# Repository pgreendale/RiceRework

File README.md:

# RiceR - A rework of the Rice contact mic preamp 

This project is based on the initial work of Alexander Rice and its successors especially the design from [Zach Poff](https://www.zachpoff.com/resources/alex-rice-piezo-preamplifier/), which caught my interest as a PCB layout was provided. He also mentions Charles Staffeld from [Sagittronics](https://sagittronics.wordpress.com/2019/07/04/simple-phantom-power-preamp-alex-rice-piezo-amplifier/), who has done extensive simulation of the original circuit. This is of significant importance looking into the input impedances of your mixing or recording device (whatever your phantom source is) putting load on the AC (signal-) path. 
That explained a lot to me when I was exploring reasons for the low gain performance of my built copies of the Rice preamp (around 9dB was the most common case). 

The design itself is [KISS](https://en.wikipedia.org/wiki/KISS_principle), it is understood and the mentioned sources provie good desings, so why these effords? 

Because we <b>can</b> (make it always better).

## Thoughts 
The <b>J201</b>-based design is biased around <i>0.5mA</i> current, [Sagittronics](https://sagittronics.wordpress.com/2019/07/04/simple-phantom-power-preamp-alex-rice-piezo-amplifier/) uses <b>2N3819</b>s with <i>1mA</i> current source. Double current means 4 times  signal power with $`P=I^2*R`$. Can we do more?

### Input impedance and source current
We want 1.228$`V_{eff}`$ (+ 4dBu) at our recorder inputs for a starting point. The design overall is a symmetrical differential amplifier, so we split our amplitude to 1/2 excursion from 0 to the <i>+</i> and <i>-</i> signal input. We assume 2 times 3.6k AC load in parallel (e.G. for Zoom recorders, Sagittronics mentioned) and get roughly

$`I = 2 \cdot I_{signal} = 2 \cdot \frac{\frac{1.228 V }{2}}{3.6kOhm}`$. 

This calculates to 0.171mA per line and sums up to <b>0.341mA</b>. In case of having less than .5mA available, we can experience gain degradation due to current-limiting at the source. This is why the 2N3819 variant does <b>14dB</b> Voltage gain at low input impedances, compared to my <i>measured 9dB</i> for the J201 configuration, around 6dB more amplitude. 

You can choose recorders with High-Z at their inputs to compensate for that, but if you're in the fields for recording, you may find restrictions at having only your already chosen and beloved recording device. Mixers like Mackie's [VLZ04](https://mackie.com/img/file_resources/1604VLZ4_OM.pdf) has 2.5k at its microphone inputs, thus fulfilling input impedance with 10 times the 220Ohm Microphone impedance, but also a non High-Z load in the AC path. 

### Maximum Voltage excursion
If we have an recorder with High-Z input, we can calculate the maximum voltage change at the 6.8k resistors from inside your recording devices phantom power circuit. They are used as drain resistors here, so current change means changing voltage drop at the resistors, the AC part (our signal) is decoupled internally with capacitors. At 0.5mA, there are +/- 0.25mA per (differential) signal input, if we change input so that one line goes towards up until Phantom power (zero current over the injection resistor), the other one is pulled down towards ground, we got $`V_{eff}=3.4 V`$ (from 0.5mA * 6.8k) difference at maximum (we avoid thinking about clipping, and the JFETs nonlinear behavior at this operating point). The biasing network around the gates keeps the gate at half of the voltage drop over the current source and the amplifying JFET. Both gates are <i>floating</i> somewhere near the phantom voltage potential. 

Piezo discs as contact mics have pretty high output voltages, so we dont need as much as voltage amplification as possible, but a fair amount of output voltage swing is nice to have,(Zoom doesnt specify maximum input voltages for their [Handy Recorder](https://www.zoom-europe.com/de/handy-recorder) products , Mackie says +22dBu maximum at mic inputs for the VLZ04). We need a stronger current source to go beyond +0dB at the output. 

### JFET Types
I like the J201, but it has poor performance. Note that more recently produced J201s have less maximum saturation current in general. I tried to find some employable alternatives. 

Since JFETs have their gate implemented as reverse biased diode, the Gate of the used N-Channel J201 etc. is biased negatively as seen from source. in the worst case, the gate is tied to ground and the source just hanging at full phantom voltage. So we need to widthstand breakdown voltages $`V_{GSS}`$ as great as -48V negative voltages. This limits the set of useable JFET types somewhat, but we can minimize that a by subtracting the current source drop. 

<b>Transconductance:</b>
Small voltage changes will cause greater current changes at higher $`g_m=\frac{\Delta i_{out}}{\Delta u_{in}}`$. This results in higher voltage drop changes at the phantom power resistors. Higher $`g_m`$, more gain. 

<b>Saturation Current:</b> 
The saturation current $`I_{DS}`$ is important for the current source. You'll tie the gate to ground and put a source resistor into the current path. The JFET will limit the current if the drop voltage of the resistor exceeds the JFETs cutoff voltage.  Some J201s have so low saturation currents that even the source resistor can be dropped, so that gate and source are tied directly to ground and the JFET is running in $`I_{DSS}`$ mode at zero gate voltage. 

Saving a resistor is not our goal. External noise on both amplifier inputs is causing the current source to change its bias voltage to stabilize the current. If it is not able to do that, the amplified noise is not symmetric on both signal lines (one side may experience earlier amplitude clipping due to unsymmetric current delivery) and can't be cancelled out by the differential recorder input stage. Having a greater range of voltage swing at the current source will allow more common mode range. Higher voltage drop at the current source allows amplifier JFETs with less gate to source voltage specs.  

<b>Fun</b>
InterFet has a really interesting outline of their JFETs on their [website](https://www.interfet.com/jfet-master-table/), based on the geometry. 

| JFET Type    | $`V_{GSS}`$ min | $`I_{DSS}`$ (min)| $`g_m`$ Transconductance (min)|Noise|
|-----|-----|-----|-----|-----|
|[J201](https://www.mouser.de/datasheet/2/676/jfet_j201_j202_interfet-2887411.pdf)|-40V| 0.2mA|500µS|5nV / Hz |
|[J202](https://www.mouser.de/datasheet/2/676/jfet_j201_j202_interfet-2887411.pdf)|-40V| 0.9mA|1000µS|5nV / Hz |
|[J113](https://www.mouser.de/datasheet/2/676/jfet_j111_j112_j113a_interfet-2887724.pdf)|-40V|2mA|15000µS|1.2nV / Hz|
|[J301](https://www.mouser.de/datasheet/2/676/jfet_j308_j309_j310_interfet-2887299.pdf)|-25V|24mA|8000 µS|2nV / Hz| 
|[BF245C](https://www.nxp.com/docs/en/data-sheet/BF245A-B-C.pdf)|-30V|12mA|14000µS||
|[2N3819](https://www.interfet.com/jfet-datasheets/jfet-2n3819-interfet.pdf)|-25V|2.0mA|2000µS|7nV / Hz|

Four things can be optimized: 

- More gain from transconductance
- Higher amplitude at phantom resistors from higher current variation
- Higher common mode noise suppression by allowing the currrent source to vary more  
- Less noise  

### Phantom Power
[DIN EN 61938](https://schoeps.de/fileadmin/user_upload/user_upload/Downloads/Vortraege_Aufsaetze/Mikrofonaufsaetze/Mikrofonbuch_Kap13.pdf) defines a current of 10mA at 48V phantom voltage (phantom current at + and - signal path together).

This <b>doesn't</b> mean that <i>every</i> recording device has the capability of driving full 10mA but lets assume we have half of that available with semiprofessional equipment. 5mA current sourcing gives 2.5mA per branch in the amplifier, giving room for gain and output improvements.

## Circuit	
Please look after [Simulation](/2-Simulation/Simulation.md) detailed circuits, simulations and results of the following approaches.  

### Approach 1: Current Source with more voltage excursion 
The J201 has a low cutoff voltage, so the voltage drop over the source resistor has is small (-0.3V min according to InterFET), asking for small resistor values to archieve this at operating point. Calculation gives 600Ohm, but in real life, I used smaller values around 100-150 Ohm to set the current output higher. This hinders the current source to lower output voltage if high common mode input puts both amplifying JFETs into conduction. 

Changing the current source J3 to a J202 JFET archives this, because it needs greater source resistor values to archieve the same current limit and allows for greater common mode input without clipping to ground.  

### Approach 2: J113 and J310 JFETs in Action
J113 and J310 have higher current specs. Especially the J310 in its function as current source is run far away from pinchoff Vg with higher source resistors. This enables the current source to float more up and down and allows more CMRR suppression down to -76dB while the amp itself provides <b>15dB</b> gain with <i>loaded</i> outputs. Plus less noise coming from the JFETS. 

### Approach 3: double current source 
A last experiment to get even more CMRR suppression requires more headroom at the current source. This is archieved to two current sources in serial configuration. Simulations show up additional -4dB CMRR, so its -80dB. Interestingly, the gain <i>rises</i> another 3.5dB too. Can't explain that at the moment. 

## PCB 
### THT vs. SMD

JFETs are still in use, but THT devices (with legs to be mounted through holes in your PCB) are kind of old-fashioned. Manufacturers know that and due to more smd-oriented PCB-Design nowadays, such components become more and more rare, thus difficult to get or <i>unreasonably</i> expensive. I didnt want to buy overpriced J201's from shady e**y stores or hipster-wallet oriented offers, and so I went on with the [SMD MMBFJ201](https://www.reichelt.de/n-kanal-jfet-40v-0-2-1ma-0-35w-sot-23-mmbfj201-p360202.html?&trstct=pos_0&nbc=1) of the J201, which costs less (0.30€)  of what a is asked for [THT J201](https://www.mouser.de/ProductDetail/InterFET/J201?qs=OxRSArmBDfyvD8SbvWteMw%3D%3D).

### Making Things smaller
My goal was to fit the whole preamp into an XLR plug. The metal housing is well grounded by the recorder and acts as shield for the amplifier. 

There are two <b>caveats</b>: capacitance/charge changes in the cable between preamp and piezo and also microphonic events like tapping the connectors housing can be heard. First is caused by the cable itself acting as a microphonic capacitor between ground and signal lines and second effect comes from the piezoelectricity of the ceramic SMD capacitors. SMD PP or PE caps in 0402 size were not available (if any ever?) so thats a tradeoff.

## Mass FET Matching
The amp is a differential (thus symmetric) design. To get good performance, matched components are needed, especially the JFETs whose can deviate from the specified mean value, even if they came from the same production run. Resistors and capacitors are easier to match, you can just buy them with good specs (1% SMD resistors are not as expensive as similiar THT maybe 20 years ago)

Not perfect, but good enough: 

 * Buy some run-of-the mill china copy of a [component tester](https://www.ebay.de/itm/265065551933?hash=item3db723583d:g:t-kAAOSwvWNgNhKa&amdata=enc%3AAQAIAAAA4MVZA11pXEi%2BY8FpUKZ%2Ba6fGrj%2Bg92W5g%2BvEFuaV7X8trvuxUWNuu%2BiUo3P4QnSn8eicAGEaVRB%2BaX3sno8Zs7n9p32MTcgCp%2FKcCjfit%2Bm41IrsrzKEI65ftT0AGj6qV5wsm%2BSe9ota6LyMAYbrZ3AixUm3jQbcnIuPTjFkVYe%2Big%2BgnT9Nog9wD%2F92axCRTxBFWWMISdoD28%2FKe9K8RMAzgf7rEN7JKfyHri0wTwoJ5zPvL857RYVo45sQIgmp1lrfoy2E4d%2F9Fjsllpe8T1pWKjBM68IU9CnFLe9h732N%7Ctkp%3ABk9SR4qI0vqmYw) based on the work of [Markus Frejek and Karl-Heinz Kübbeler](https://www.mikrocontroller.net/articles/AVR_Transistortester#Hint_to_Cloners_and_Sellers_中文). The versions with the 3 SMD pads next to the test socket are good for putting JFETS with SOT-3 housing on.
 * Get [firmware souce](https://github.com/Mikrocontroller-net/transistortester/tree/master) and compile it with UART support. (I had to replace my SPI display with an I2C oled one to free pins for UART, you can also remove the display)
 * Test components: put some on, press the button verify the measurement is done 
 * Label the components! My favorite is a [glued sheet](0-Documentation/JFET_Matching.jpeg) with a table with numbers, where I put freshly tested components on. 
 * Record the UART output into a file e.g. with [putty](https://putty.org) 
 * CSV import: Use MS Excel or Libreoffice Calc to get the test parameters from the uart record text file into a spreadsheet, convert it into a table that parameters from the same component stick together
 * sort for <b>IDss</b>, <b>ID0</b> and <b>V_g at pinchoff</b> and use the most similiar parts together (same readings)

|Transistor tester lunchbox|JFETs on labeled glue sheet|
|---|---|
|||

## Finished Preamp
### Building kit 
Finished preamp housed in XLR plug, above is a prepared building kit, including matched parts and PCB. 

### Measurements with real built High-Gain preamp
These measurements were done at 
 * 48V phantom power, 6.76k resistors 
 * -11.77 dbU (200mV to 0.775V)  amplitude of the input sine  
 * 10k load resistance, roughly 5 times greater than in simulations not good in terms of comparability

|Freq.| 35Hz| 1kHz |5KhZ | 28KHz |
|---|---|---|---|---|
||  | |||
|abs. Output|  9.68dBU, HP rolloff  | 15.72dBU  | 15.12dbU  | 9.65dBU LP rolloff| 
|relative to 0.2V | 21.44dB | 27.49dB | 26.89dB | 21.42dB |

These values are nearly double the simulated gain, which could be explained with the ecxeptional high load resistance (20k in parallel). Simulating the J113/J310 circuit again results in 26dB relative gain, not that far off.  

### Clipping 
JFETs do clip soft. I am running them at 2.21dbU at the input, getting >+22dbU of output voltage swing here. Thats a LOT, ensure your recording/mixing hardware can handle such voltages, or your input protection will kick in and may get damaged (remembering those A&H DJ mixers killing Zoom recorders...?). It shall just show that the High-Gain amplifier with J113/J310 JFETs is capable of some serious voltage swing.

## Epilog
I made these kits for a workshop with non-experienced solder. If you like to build one for yourself, feel free, to use [schematic and pcb files](1-Hardware/PCB) to do your own. I still have some PCB+Parts kits (without XLR-Plug) sitting around and will sell them to you in the mentioned onepage-kit form if you contact me.  

If you like my work, support me on https://www.buymeacoffee.com/pgreendale :)

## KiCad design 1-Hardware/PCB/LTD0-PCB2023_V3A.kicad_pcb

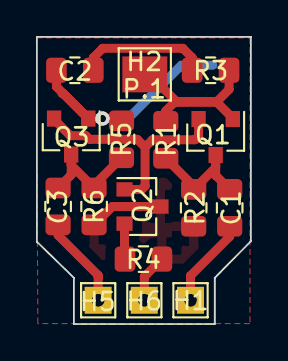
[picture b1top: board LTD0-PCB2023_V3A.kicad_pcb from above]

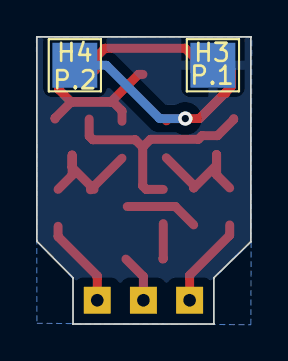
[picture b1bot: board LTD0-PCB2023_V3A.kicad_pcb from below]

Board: 2 copper layers, 11.9 x 16.0 mm, 18 parts (2 on the bottom side), 10 nets.

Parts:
C1, C3: 2.2nF; C_0805_2012Metric_Pad1.15x1.40mm_HandSolder
C2: 680pf; C_0805_2012Metric_Pad1.15x1.40mm_HandSolder
H1: Mic +; TestPoint_THTPad_1.5x1.5mm_Drill0.7mm
H2: XLR +; TestPoint_Pad_2.5x2.5mm
H3: XLR GND; TestPoint_Pad_2.5x2.5mm
H4: XLR -; TestPoint_Pad_2.5x2.5mm
H5: Mic -; TestPoint_THTPad_1.5x1.5mm_Drill0.7mm
H6: Mic GND; TestPoint_THTPad_1.5x1.5mm_Drill0.7mm
Q1, Q2, Q3: MMBFJ201; SOT-23
R1, R2, R5: 3.3M; R_0805_2012Metric_Pad1.15x1.40mm_HandSolder
R3: 150R; R_0805_2012Metric_Pad1.15x1.40mm_HandSolder
R4: 0.5-1.2k; R_0805_2012Metric_Pad1.15x1.40mm_HandSolder
R6: 3M; R_0805_2012Metric_Pad1.15x1.40mm_HandSolder

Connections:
GND: H3.GND, H6.GND, Q2.3, R2.2, R4.2, R6.2
unnamed: C1.1, Q1.3, R1.2, R2.1
unnamed: C1.2, H1.M-
unnamed: C2.1, H4.+, Q3.1, R5.1
unnamed: C2.2, R3.2
unnamed: C3.1, H5.M+
unnamed: C3.2, Q3.3, R5.2, R6.1
unnamed: H2.-, Q1.1, R1.1, R3.1
unnamed: Q1.2, Q2.1, Q3.2
unnamed: Q2.2, R4.1

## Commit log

2024-01-24 Add files via upload
    Initial Upload
2024-01-24 update file structures, foledernames with no whitespaces
2024-01-24 update deleted folders
2024-01-28 Update README.md
    buymeacffe
2024-01-28 Update README.md
    Simulation correction
